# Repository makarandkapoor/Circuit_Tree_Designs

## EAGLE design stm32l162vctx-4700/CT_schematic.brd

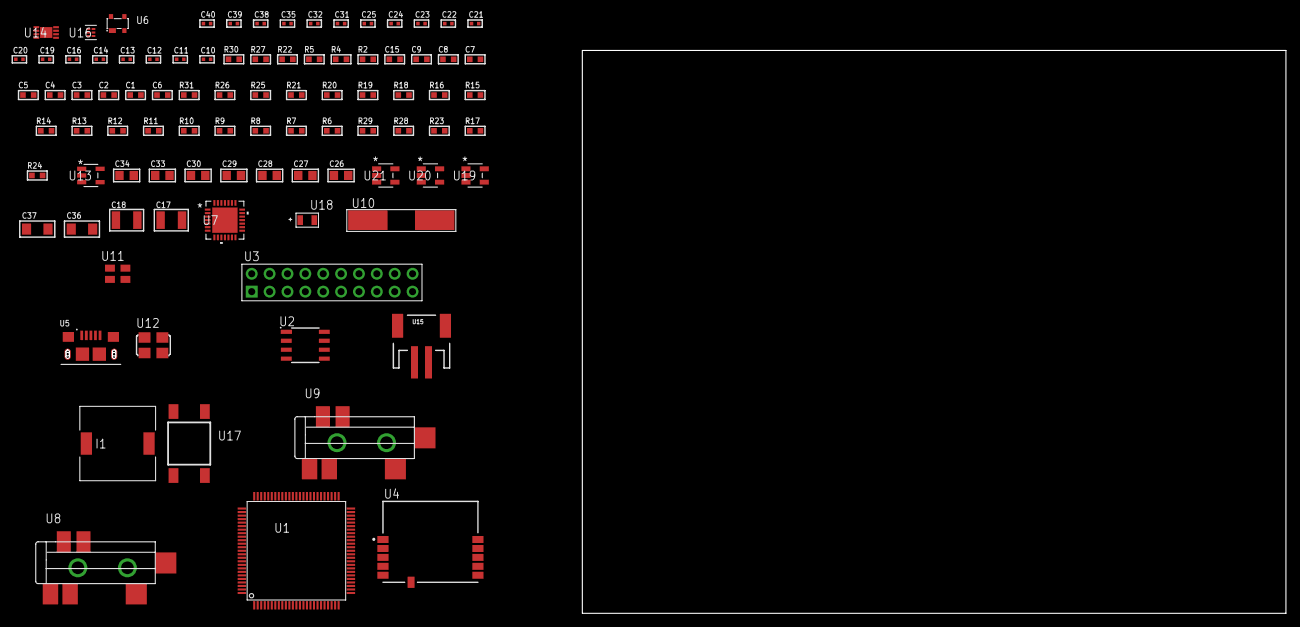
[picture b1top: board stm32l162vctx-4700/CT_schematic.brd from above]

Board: 2 copper layers, 91 parts (0 on the bottom side), 50 nets, no tracks yet.

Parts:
C1, C2, C3, C4, C5, C7: 1e-07; C0603
C6: 4.7e-06; C0603
C8: 1e-08; C0603
C9, C15: 1e-06; C0603
C10, C11: 1e-11; C0402
C12, C31, C32, C38, C39, C40: 1e-08; C0402
C13, C14, C16, C21, C22, C23, C24, C25, C35: 1e-07; C0402
C17, C18: 2.2e-05; C1210
C19, C20: 1e-09; C0402
C26, C27, C28, C29, C30, C33, C34: 1e-05; C0805
C36, C37: 1e-05; C1206
I1: 3.8e-06; DR1040
R2: 1000.0; R0603
R4, R5: 4700.0; R0603
R6, R7, R8, R9, R10, R11, R12, R13, R14, R15, R16, R25, R26, R31: 10000.0; R0603
R17: 100000.0; R0603
R18, R19, R20, R21: 47000.0; R0603
R22: 680.0; R0603
R23: 220000.0; R0603
R24: 1000000.0; R0603
R27: 9100.0; R0603
R28: 680000.0; R0603
R29: 120000.0; R0603
R30: 2000.0; R0603
U1: STM32L162VCTx; LQFP100
U2: AT25020B-SSHL-T; SOIC-8
U3: TST-110-05-T-D-RA
U4: SPBTLE-RF; XCVR_SPBTLE-RF
U5: 10118193-0001LF; FCI_10118193-0001LF
U6: prtr5v0u2ax; SOT143B
U7: WM8731CLSEFL; QFN-28
U8, U9: SJ-43515TS-SMT-TR
U10: ABLS-25.000MHZ-B2F-T
U11: ASEK-32.768KHz-ECST; ASEK
U12: ASFL1-12.288MHZ-EC-T; ASFL1
U13: ltc3406es5; TSOT-23-5
U14: MCP73831T-2ACI/MC; DFN8_2X3MC
U15: S2B-PH-SM4-TB(LF)(SN); JST-2-SMD
U16: TPS3895ADRYR; SON-6
U17: 4-1437565-2; SW_4-1437565-2
U18: Q65110A2395; LGM67K-G1J2-24-Z
U19, U20, U21: nc7sz125m5x; NC7SZ125M5X

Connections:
CLK_CRYSTAL_U1_12: C10.1, U1.12, U10.1
CLK_CRYSTAL_U1_13: C11.1, U1.13, U10.2
CLK_U1_8: U1.8, U11.3
CLK_U7_1: U7.1, U12.3
GND: C1.2, C2.2, C3.2, C4.2, C5.2, C6.2, C7.2, C8.2, C9.2, C10.2, C11.2, C12.2, C13.2, C14.2, C15.2, C16.2, C20.2, C21.2, C22.2, C23.2, C24.2, C25.2, C26.2, C27.2, C28.2, C29.2, C30.2, C31.2, C32.2, C33.2, C34.1, C34.2, C35.2, C36.2, C37.2, C38.2, C39.2, C40.2, R2.2, R6.2, R15.2, R17.2, R18.2, R19.2, R20.2, R21.2, R23.2, R27.2, R29.2, R30.2, U1.10, U1.19, U1.20, U1.27, U1.49, U1.74, U1.99, U2.4, U3.4, U3.6, U3.8, U3.10, U3.12, U3.14, U3.16, U3.18, U3.20, U4.6, U5.5, U5.6, U5.7, U5.8, U5.9, U6.1, U7.4, U7.15, U7.19, U7.25, U7.26, U7.29, U8.1, U9.1, U11.2, U12.2, U13.2, U14.6, U14.9, U15.2, U16.2, U18.C, U19.2, U19.3, U20.1, U20.3, U21.1, U21.3
INPUT_USBPOWER_5V: C36.1, R31.2, U5.1, U6.4, U14.1, U14.2
NET_U1_6: C7.1, U1.6
NET_U1_14: R5.1, U1.14, U21.4
NET_U1_22: C8.1, C9.1, U1.21, U1.22
NET_U1_94: R6.1, U1.94
NET_U1_98: U17.3, U17.4
NET_U2_3: R7.1, U2.3
NET_U2_7: R9.1, U2.7
NET_U3_19: R15.1, U3.19
NET_U4_11: R4.1, U4.11, U20.4
NET_U7_20: C25.1, C30.1, U7.20
NET_U8_2: C18.1, R20.1, U8.2
NET_U8_5: C17.1, R19.1, U8.5
NET_U9_5: C19.1, C20.1, R21.1, R22.1, U9.5
NET_U13_3: I1.1, U13.3
NET_U13_5: R23.1, R24.1, U13.5
NET_U13_ATNET_3: I1.2, R24.2
NET_U14_5: R31.1, U14.5
NET_U14_8: R30.1, U14.8
NET_U16_1: R26.1, R27.1, U16.1
NET_U16_3: R28.2, R29.1, U16.3
NET_U16_4: R25.1, U16.4, U19.4, U20.2, U21.2
NET_U17_1: R2.1, U17.1, U17.2
PROC_GPIO_TO_U4_SPI_IRQ: R18.1, U1.1, U4.4
PROC_I2S2_CK: U1.82, U7.7
PROC_I2S2_SD: U1.85, U7.8
PROC_I2S2_WS: U1.81, U7.9, U7.11
PROC_SPI1_MISO: U1.31, U4.8
PROC_SPI1_MOSI: U1.32, U4.9
PROC_SPI1_NSS: R16.1, U1.29, U4.10
PROC_SPI1_SCK: R17.1, U1.30, U4.7
PROC_SPI2_MISO: U1.53, U2.2
PROC_SPI2_MOSI: U1.54, U2.5
PROC_SPI2_NSS: R8.1, U1.51, U2.1
PROC_SPI2_SCK: U1.52, U2.6
PROC_SYS_JTCK_SWCLK: R13.1, U1.76, U3.9
PROC_SYS_JTDI: R11.1, U1.77, U3.5
PROC_SYS_JTDO_TRACESWO: U1.89, U3.13
PROC_SYS_JTMS_SWDIO: R12.1, U1.72, U3.7
PROC_SYS_JTRST: R10.1, U1.90, U3.3
PROC_USB_DM: U1.70, U5.2, U6.3
PROC_USB_DP: U1.71, U5.3, U6.2
RST_OUT_U3_SRESET_B: R14.1, U3.15, U19.1
VCC_S1_3V7: C33.1, C37.1, U13.4, U14.3, U14.4, U15.1
VCC_TIER1_3V3: C1.1, C2.1, C3.1, C4.1, C5.1, C6.1, C12.1, C13.1, C14.1, C15.1, C16.1, C21.1, C22.1, C23.1, C24.1, C26.1, C27.1, C28.1, C29.1, C31.1, C32.1, C34.2, C35.1, C38.1, C39.1, C40.1, I1.2, R4.2, R5.2, R7.2, R8.2, R9.2, R10.2, R11.2, R12.2, R13.2, R14.2, R16.2, R24.2, R25.2, R26.2, R28.1, U1.11, U1.28, U1.50, U1.75, U1.100, U2.8, U3.1, U3.2, U4.5, U7.3, U7.5, U7.12, U7.18, U11.4, U12.4, U16.6, U19.5, U20.5, U21.5

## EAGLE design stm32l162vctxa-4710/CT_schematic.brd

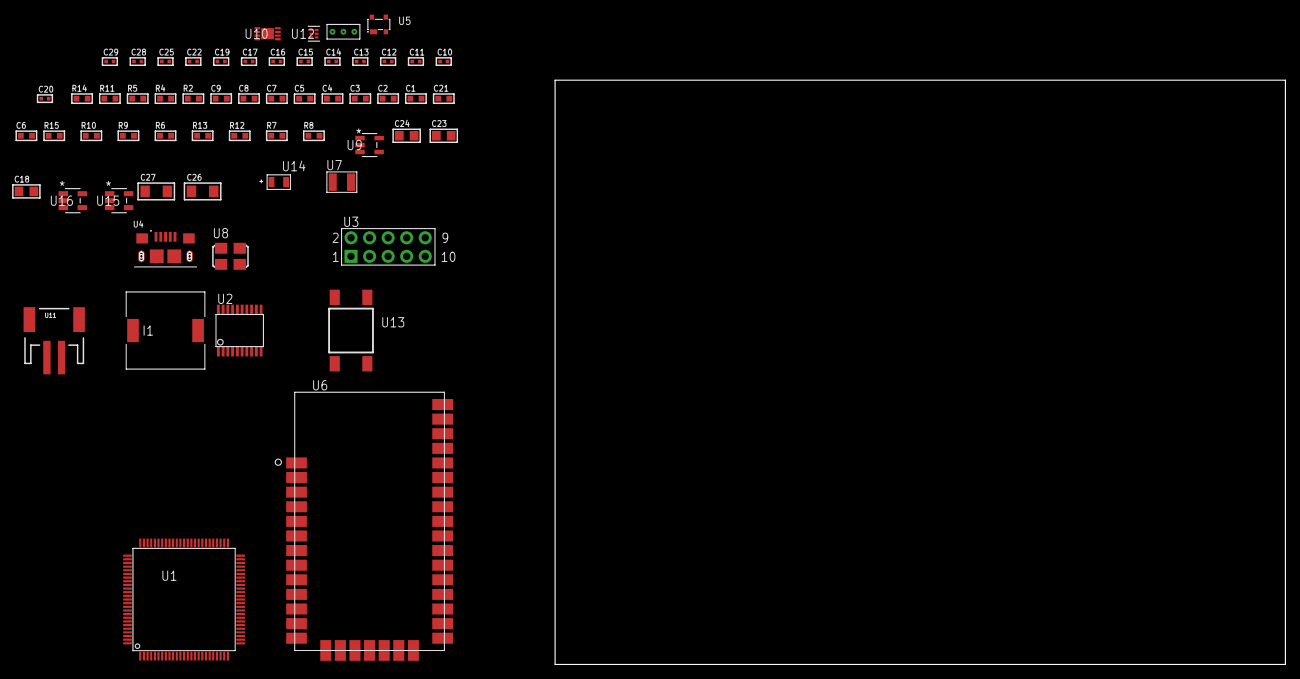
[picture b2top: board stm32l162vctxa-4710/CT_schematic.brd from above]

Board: 2 copper layers, 60 parts (0 on the bottom side), 43 nets, no tracks yet.

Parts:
C1, C2, C3, C4, C5, C7: 1e-07; C0603
C6: 4.7e-06; C0603
C8: 1e-08; C0603
C9: 1e-06; C0603
C10, C11: 1e-11; C0402
C12, C13, C14, C15, C16, C17, C19, C25: 1e-07; C0402
C18, C23, C24: 1e-05; C0805
C20: 4.7e-11; C0402
C21: 8.2e-12; C0603
C22, C28, C29: 1e-08; C0402
C26, C27: 1e-05; C1206
I1: 3.8e-06; DR1040
R2: 1000.0; R0603
R4, R5: 4700.0; R0603
R6, R9, R10, R15: 10000.0; R0603
R7: 220000.0; R0603
R8: 1000000.0; R0603
R11: 9100.0; R0603
R12: 680000.0; R0603
R13: 120000.0; R0603
R14: 2000.0; R0603
U1: STM32L162VCT6A; LQFP100
U2: SP3203ECY-L/TR; TSSOP20-I
U3: HTSS-105-01-G-D
U4: 10118193-0001LF; FCI_10118193-0001LF
U5: prtr5v0u2ax; SOT143B
U6: XB24CZ7UIS-004
U7: ABS07-32.768KHZ-7-T
U8: ASFL1-25MHZ-NCS; ASFL1
U9: ltc3406es5; TSOT-23-5
U10: MCP73831T-2ACI/MC; DFN8_2X3MC
U11: S2B-PH-SM4-TB(LF)(SN); JST-2-SMD
U12: TPS3895ADRYR; SON-6
U13: 4-1437565-2; SW_4-1437565-2
U14: Q65110A2395; LGM67K-G1J2-24-Z
U15, U16: nc7sz125m5x; NC7SZ125M5X
U17: Dummy; DUMMY_PACKAGE_131

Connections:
CLK_CRYSTAL_U1_8: C10.1, U1.8, U7.1
CLK_CRYSTAL_U1_9: C11.1, U1.9, U7.2
CLK_U1_12: U1.12, U8.3
GND: C1.2, C2.2, C3.2, C4.2, C5.2, C6.2, C7.2, C8.2, C9.2, C10.2, C11.2, C12.2, C13.2, C16.2, C17.2, C18.2, C19.2, C20.2, C21.2, C22.2, C23.2, C24.1, C24.2, C25.2, C26.2, C27.2, C28.2, C29.2, R2.2, R6.2, R7.2, R11.2, R13.2, R14.2, U1.10, U1.19, U1.20, U1.27, U1.49, U1.74, U1.99, U2.18, U3.9, U4.5, U4.6, U4.7, U4.8, U4.9, U5.1, U6.1, U6.11, U6.13, U6.22, U6.35, U8.2, U9.2, U10.6, U10.9, U11.2, U12.2, U14.C, U15.1, U15.3, U16.1, U16.3, U17.1
INPUT_USBPOWER_5V: C26.1, R15.2, U4.1, U5.4, U10.1, U10.2
NET_U1_6: C7.1, U1.6
NET_U1_14: R5.1, U1.14, U16.4
NET_U1_94: R6.1, U1.94
NET_U1_98: U13.3, U13.4
NET_U2_1: C14.1, U2.1
NET_U2_2: C16.1, U2.2
NET_U2_3: C14.2, U2.3
NET_U2_4: C15.1, U2.4
NET_U2_5: C15.2, U2.5
NET_U2_6: C17.1, U2.6
NET_U3_3: U2.14, U3.3
NET_U3_4: U2.13, U3.4
NET_U3_5: U2.17, U3.5
NET_U3_6: U2.16, U3.6
NET_U6_6: R4.1, U6.6, U15.4
NET_U9_3: I1.1, U9.3
NET_U9_5: R7.1, R8.1, U9.5
NET_U9_ATNET_3: I1.2, R8.2
NET_U10_5: R15.1, U10.5
NET_U10_8: R14.1, U10.8
NET_U12_1: R10.1, R11.1, U12.1
NET_U12_3: R12.2, R13.1, U12.3
NET_U12_4: R9.1, U12.4, U15.2, U16.2
NET_U13_1: R2.1, U13.1, U13.2
PROC_PE2: U1.1, U17.2
PROC_PE3: U1.2, U17.3
PROC_SPI1_MISO: U1.31, U6.17
PROC_SPI1_MOSI: U1.32, U6.16
PROC_SPI1_NSS: U1.29, U6.15
PROC_SPI1_SCK: U1.30, U6.14
PROC_USART2_CTS: U1.23, U2.8
PROC_USART2_RTS: U1.24, U2.10
PROC_USART2_RX: U1.26, U2.11
PROC_USART2_TX: U1.25, U2.7
PROC_USB_DM: U1.70, U4.2, U5.3
PROC_USB_DP: U1.71, U4.3, U5.2
VCC_S1_3V7: C23.1, C27.1, U9.4, U10.3, U10.4, U11.1
VCC_TIER1_3V3: C1.1, C2.1, C3.1, C4.1, C5.1, C6.1, C8.1, C9.1, C12.1, C13.1, C18.1, C19.1, C20.1, C21.1, C22.1, C24.2, C25.1, C28.1, C29.1, I1.2, R4.2, R5.2, R8.2, R9.2, R10.2, R12.1, U1.11, U1.21, U1.22, U1.28, U1.50, U1.75, U1.100, U2.12, U2.19, U6.2, U6.27, U8.4, U12.6, U15.5, U16.5

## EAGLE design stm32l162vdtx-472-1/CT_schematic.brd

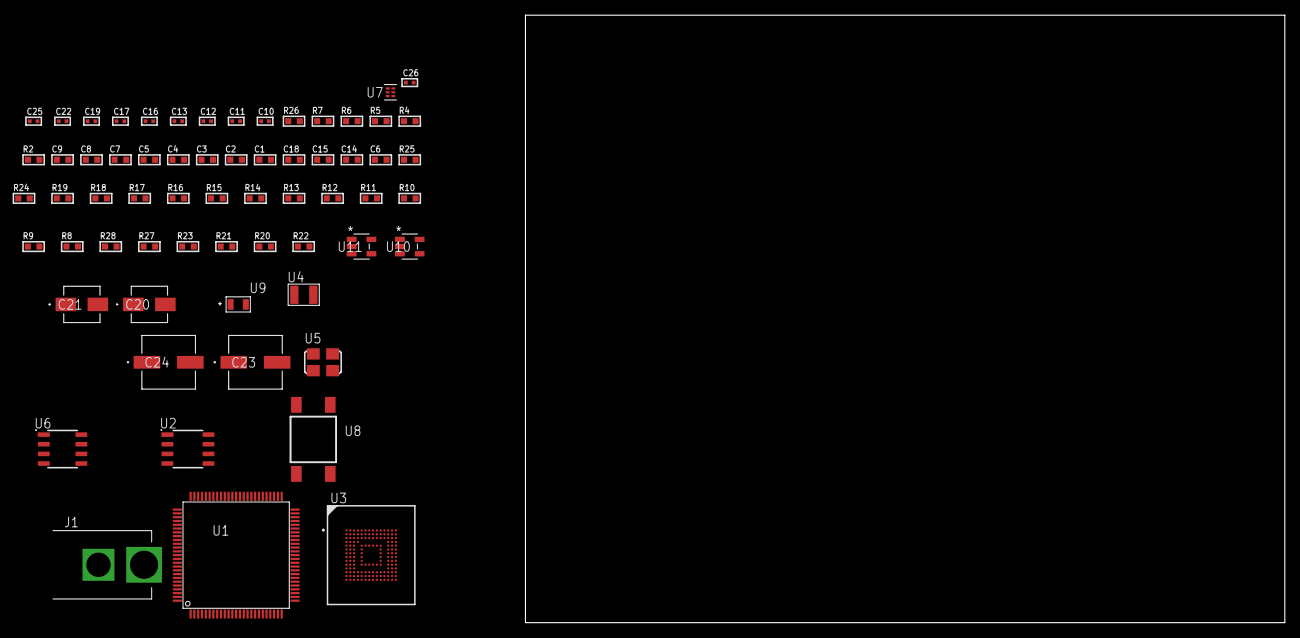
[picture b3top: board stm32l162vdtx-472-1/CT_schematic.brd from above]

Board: 2 copper layers, 100.0 x 80.0 mm, 64 parts (0 on the bottom side), 32 nets, no tracks yet.

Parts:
C1, C2, C3, C4, C5, C7: 1e-07; C0603
C6: 4.7e-06; C0603
C8: 1e-08; C0603
C9: 1e-06; C0603
C10, C11: 1e-11; C0402
C12, C19, C25, C26: 1e-08; C0402
C13, C16, C17, C22: 1e-07; C0402
C14, C15, C18: 2.2e-06; C0603
C20: 1e-06; EXV-9B
C21: 2.2e-06; EXV-9B
C23, C24: 0.0001; EXV-9H
J1: PJ-037B; PJ-037B_PACKAGE
R2: 1000.0; R0603
R4, R5: 4700.0; R0603
R6, R7: 2200.0; R0603
R8, R9, R24, R25: 10000.0; R0603
R10, R11, R12, R13, R14, R15, R16, R17, R18, R19: 34000.0; R0603
R20, R21, R23: 100000.0; R0603
R22: 164658.62; R0603
R26: 9100.0; R0603
R27: 680000.0; R0603
R28: 120000.0; R0603
U1: STM32L162VDT6; LQFP100
U2: M24M02-DRMN6TP; SOIC-8
U3: mtfc4gmcdm; TFBGA-153
U4: ABS07-32.768KHZ-7-T
U5: ASFL1-25MHZ-NCS; ASFL1
U6: LP2954AIMX/NOPB; LP2954
U7: TPS3895ADRYR; SON-6
U8: 4-1437565-2; SW_4-1437565-2
U9: Q65110A2395; LGM67K-G1J2-24-Z
U10, U11: nc7sz125m5x; NC7SZ125M5X

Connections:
CLK_CRYSTAL_U1_8: C10.1, U1.8, U4.1
CLK_CRYSTAL_U1_9: C11.1, U1.9, U4.2
CLK_U1_12: U1.12, U5.3
GND: C1.2, C2.2, C3.2, C4.2, C5.2, C6.2, C7.2, C8.2, C9.2, C10.2, C11.2, C12.2, C13.2, C14.2, C15.2, C16.2, C17.2, C18.2, C19.2, C20.2, C21.2, C22.2, C23.2, C24.2, C25.2, C26.2, J1.2, R2.2, R8.2, R9.2, R23.2, R26.2, R28.2, U1.10, U1.19, U1.20, U1.27, U1.49, U1.74, U1.99, U2.4, U3.C4, U3.E7, U3.G5, U3.H10, U3.K8, U3.N2, U3.N5, U3.P4, U3.P6, U5.2, U6.4, U7.2, U9.C, U10.1, U10.3, U11.1, U11.3
NET_U1_6: C7.1, U1.6
NET_U1_14: R5.1, U1.14, U11.4
NET_U1_92: R6.1, U1.92, U2.6
NET_U1_93: R7.1, U1.93, U2.5
NET_U1_94: R8.1, U1.94
NET_U1_98: U8.3, U8.4
NET_U2_3: R9.1, U2.3
NET_U3_C2: C15.1, C16.1, U3.C2
NET_U3_K5: R4.1, U3.K5, U10.4
NET_U6_3: R21.1, U6.3
NET_U6_5: R20.1, U6.5
NET_U6_7: R22.2, R23.1, U6.7
NET_U7_1: R25.1, R26.1, U7.1
NET_U7_3: R27.2, R28.1, U7.3
NET_U7_4: R24.1, U7.4, U10.2, U11.2
NET_U8_1: R2.1, U8.1, U8.2
PROC_SDIO_CK: R19.1, U1.80, U3.M6
PROC_SDIO_CMD: R18.1, U1.83, U3.M5
PROC_SDIO_D0: R10.1, U1.65, U3.A3
PROC_SDIO_D1: R11.1, U1.66, U3.A4
PROC_SDIO_D2: R12.1, U1.78, U3.A5
PROC_SDIO_D3: R13.1, U1.79, U3.B2
PROC_SDIO_D4: R14.1, U1.95, U3.B3
PROC_SDIO_D5: R15.1, U1.96, U3.B4
PROC_SDIO_D6: R16.1, U1.63, U3.B5
PROC_SDIO_D7: R17.1, U1.64, U3.B6
VCC_S1_7V2: C20.1, C23.1, C24.1, J1.1, R21.2, U6.8
VCC_TIER1_3V3: C1.1, C2.1, C3.1, C4.1, C5.1, C6.1, C8.1, C9.1, C12.1, C13.1, C14.1, C17.1, C18.1, C19.1, C21.1, C22.1, C25.1, C26.1, R4.2, R5.2, R6.2, R7.2, R10.2, R11.2, R12.2, R13.2, R14.2, R15.2, R16.2, R17.2, R18.2, R19.2, R20.2, R22.1, R24.2, R25.2, R27.1, U1.11, U1.21, U1.22, U1.28, U1.50, U1.75, U1.100, U2.8, U3.C6, U3.E6, U3.F5, U3.J10, U3.K9, U3.M4, U3.N4, U3.P3, U3.P5, U5.4, U6.1, U7.6, U10.5, U11.5

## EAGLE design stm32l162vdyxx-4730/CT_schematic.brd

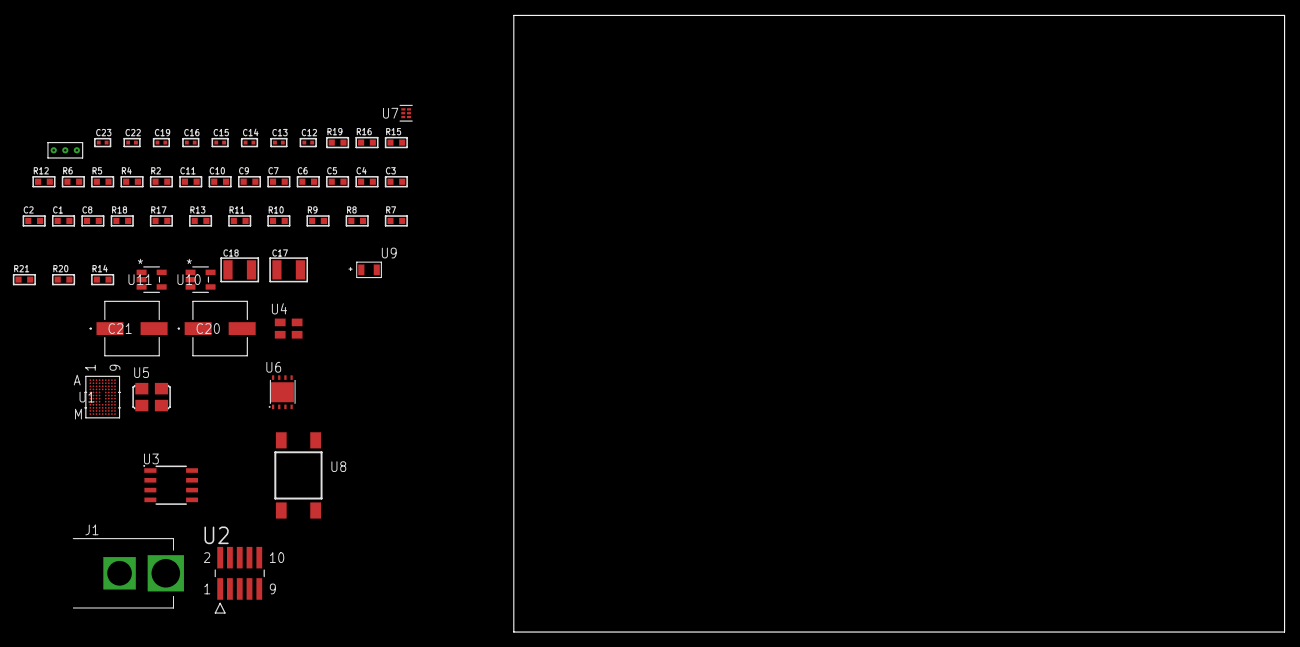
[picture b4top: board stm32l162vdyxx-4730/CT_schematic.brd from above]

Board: 2 copper layers, 100.0 x 80.0 mm, 55 parts (0 on the bottom side), 27 nets, no tracks yet.

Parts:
C1, C2, C3, C4, C5, C6, C7, C9: 1e-07; C0603
C8: 4.7e-06; C0603
C10: 1e-08; C0603
C11: 1e-06; C0603
C12, C19: 1e-07; C0402
C13, C14, C15, C16, C22, C23: 1e-08; C0402
C17, C18: 1e-05; C1210
C20, C21: 0.0001; EXV-9H
J1: PJ-037B; PJ-037B_PACKAGE
R2, R16: 1000.0; R0603
R4: 4700.0; R0603
R5, R6: 2200.0; R0603
R7, R8, R9, R10, R11, R13, R17, R18: 10000.0; R0603
R12: 5.0; R0603
R14: 100000.0; R0603
R15: 2231.0; R0603
R19: 9100.0; R0603
R20: 680000.0; R0603
R21: 120000.0; R0603
U1: STM32L162VDY6X; WLCSP104
U2: FTSH-105-01-L-DV-K; SAMTEC_FTSH-105-01-L-DV-K
U3: M24M02-DRMN6TP; SOIC-8
U4: ASEK-32.768KHz-ECST; ASEK
U5: ASFL1-25MHZ-NCS; ASFL1
U6: LP3878SDX-ADJ/NOPB; WSON-8
U7: TPS3895ADRYR; SON-6
U8: 4-1437565-2; SW_4-1437565-2
U9: Q65110A2395; LGM67K-G1J2-24-Z
U10, U11: nc7sz125m5x; NC7SZ125M5X
U12: Dummy; DUMMY_PACKAGE_121

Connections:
CLK_U1_D8: U1.D8, U4.3
CLK_U1_F8: U1.F8, U5.3
GND: C1.2, C2.2, C3.2, C4.2, C5.2, C6.2, C7.2, C8.2, C9.2, C10.2, C11.2, C12.2, C13.2, C14.2, C15.2, C16.2, C17.2, C18.2, C19.2, C20.2, C21.2, C22.2, C23.2, J1.2, R2.2, R7.2, R11.2, R12.2, R13.2, R16.2, R19.2, R21.2, U1.A1, U1.C7, U1.D2, U1.E8, U1.H8, U1.J9, U1.K8, U1.L2, U1.M1, U2.3, U2.5, U3.4, U4.2, U5.2, U6.3, U6.PAD, U7.2, U9.C, U10.2, U10.3, U11.1, U11.3, U12.1
NET_U1_A7: R7.1, U1.A7
NET_U1_B6: R6.1, U1.B6, U3.5
NET_U1_C5: R5.1, U1.C5, U3.6
NET_U1_E7: C9.1, U1.E7
NET_U1_F7: R4.1, U1.F7, U11.4
NET_U1_M8: U8.3, U8.4
NET_U2_9: R12.1, U2.9
NET_U3_3: R13.1, U3.3
NET_U6_1: C16.1, U6.1
NET_U6_6: R15.2, R16.1, U6.6
NET_U6_8: R14.1, U6.8
NET_U7_1: R18.1, R19.1, U7.1
NET_U7_3: R20.2, R21.1, U7.3
NET_U7_4: R17.1, U7.4, U10.4, U11.2
NET_U8_1: R2.1, U8.1, U8.2
PROC_SYS_JTCK_SWCLK: R11.1, U1.D3, U2.4
PROC_SYS_JTDI: R9.1, U1.B1, U2.8
PROC_SYS_JTDO_TRACESWO: U1.B5, U2.6
PROC_SYS_JTMS_SWDIO: R10.1, U1.E3, U2.2
PROC_TIM10_CH1: U1.B7, U12.2
PROC_TIM11_CH1: U1.A8, U12.3
RST_OUT_U2_JTAG_RST_B: R8.1, U2.10, U10.1
VCC_S1_12V4: C17.1, C20.1, C21.1, J1.1, R14.2, U6.4
VCC_TIER1_3V3: C1.1, C2.1, C3.1, C4.1, C5.1, C6.1, C7.1, C8.1, C10.1, C11.1, C12.1, C13.1, C14.1, C15.1, C18.1, C19.1, C22.1, C23.1, R4.2, R5.2, R6.2, R8.2, R9.2, R10.2, R15.1, R17.2, R18.2, R20.1, U1.A9, U1.B8, U1.C1, U1.E9, U1.G6, U1.G7, U1.K3, U1.L8, U1.M9, U2.1, U3.8, U4.4, U5.4, U6.5, U7.6, U10.5, U11.5

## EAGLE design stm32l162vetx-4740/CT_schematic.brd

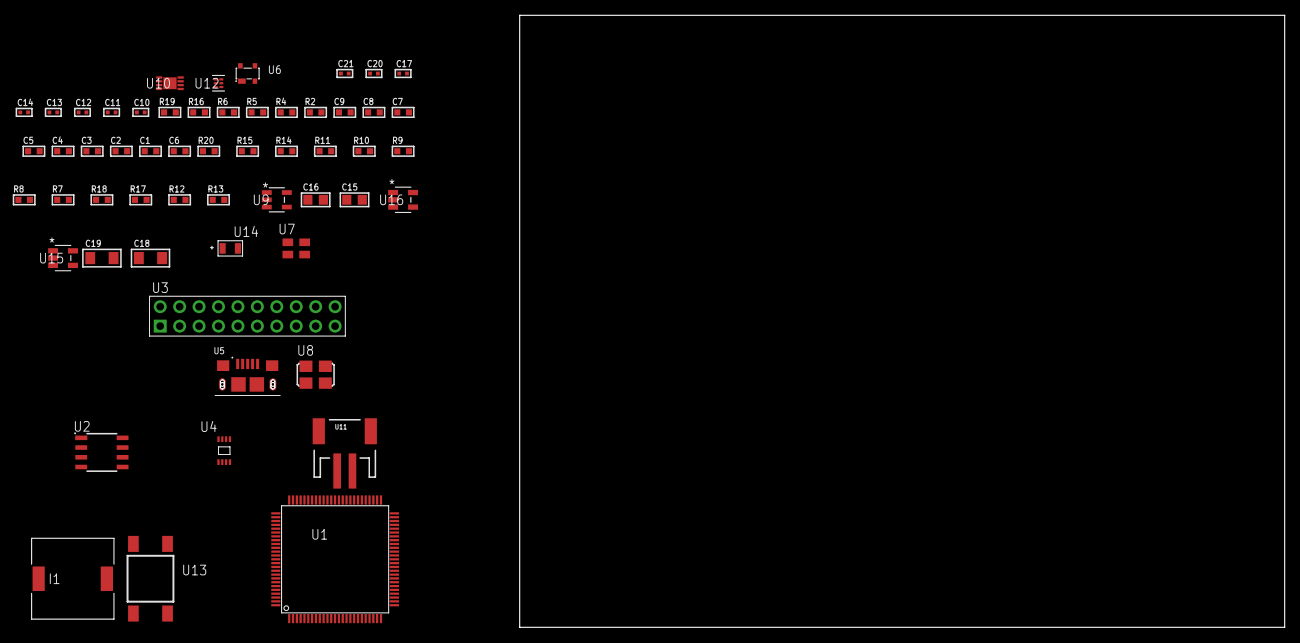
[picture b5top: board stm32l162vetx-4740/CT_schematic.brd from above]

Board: 2 copper layers, 56 parts (0 on the bottom side), 33 nets, no tracks yet.

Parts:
C1, C2, C3, C4, C5, C7: 1e-07; C0603
C6: 4.7e-06; C0603
C8: 1e-08; C0603
C9: 1e-06; C0603
C10, C12, C13, C14, C20, C21: 1e-08; C0402
C11, C17: 1e-07; C0402
C15, C16: 1e-05; C0805
C18, C19: 1e-05; C1206
I1: 3.8e-06; DR1040
R2: 1000.0; R0603
R4: 4700.0; R0603
R5, R6: 2200.0; R0603
R7, R8, R9, R10, R11, R14, R15, R20: 10000.0; R0603
R12: 220000.0; R0603
R13: 1000000.0; R0603
R16: 9100.0; R0603
R17: 680000.0; R0603
R18: 120000.0; R0603
R19: 2000.0; R0603
U1: STM32L162VET6; LQFP100
U2: AT25160B-SSHL-T; SOIC-8
U3: TST-110-05-T-D-RA
U4: 24AA08T-I/MNY; TDFN-8/6MM
U5: 10118193-0001LF; FCI_10118193-0001LF
U6: prtr5v0u2ax; SOT143B
U7: ASEK-32.768KHz-ECST; ASEK
U8: ASFL1-25MHZ-NCS; ASFL1
U9: ltc3406es5; TSOT-23-5
U10: MCP73831T-2ACI/MC; DFN8_2X3MC
U11: S2B-PH-SM4-TB(LF)(SN); JST-2-SMD
U12: TPS3895ADRYR; SON-6
U13: 4-1437565-2; SW_4-1437565-2
U14: Q65110A2395; LGM67K-G1J2-24-Z
U15, U16: nc7sz125m5x; NC7SZ125M5X

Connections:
CLK_U1_8: U1.8, U7.3
CLK_U1_12: U1.12, U8.3
GND: C1.2, C2.2, C3.2, C4.2, C5.2, C6.2, C7.2, C8.2, C9.2, C10.2, C11.2, C12.2, C13.2, C14.2, C15.2, C16.1, C16.2, C17.2, C18.2, C19.2, C20.2, C21.2, R2.2, R7.2, R12.2, R16.2, R18.2, R19.2, U1.10, U1.19, U1.20, U1.27, U1.49, U1.74, U1.99, U2.4, U3.4, U3.6, U3.8, U3.10, U3.12, U3.14, U3.16, U3.18, U3.20, U4.4, U5.5, U5.6, U5.7, U5.8, U5.9, U6.1, U7.2, U8.2, U9.2, U10.6, U10.9, U11.2, U12.2, U14.C, U15.2, U15.3, U16.1, U16.3
INPUT_USBPOWER_5V: C18.1, R20.2, U5.1, U6.4, U10.1, U10.2
NET_U1_6: C7.1, U1.6
NET_U1_14: R4.1, U1.14, U16.4
NET_U1_92: R5.1, U1.92, U4.6
NET_U1_93: R6.1, U1.93, U4.5
NET_U1_94: R7.1, U1.94
NET_U1_98: U13.3, U13.4
NET_U2_3: R8.1, U2.3
NET_U2_7: R10.1, U2.7
NET_U9_3: I1.1, U9.3
NET_U9_5: R12.1, R13.1, U9.5
NET_U9_ATNET_3: I1.2, R13.2
NET_U10_5: R20.1, U10.5
NET_U10_8: R19.1, U10.8
NET_U12_1: R15.1, R16.1, U12.1
NET_U12_3: R17.2, R18.1, U12.3
NET_U12_4: R14.1, U12.4, U15.4, U16.2
NET_U13_1: R2.1, U13.1, U13.2
PROC_SPI1_MISO: U1.31, U2.2
PROC_SPI1_MOSI: U1.32, U2.5
PROC_SPI1_NSS: R9.1, U1.29, U2.1
PROC_SPI1_SCK: U1.30, U2.6
PROC_SYS_JTCK_SWCLK: U1.76, U3.9
PROC_SYS_JTDO_TRACESWO: U1.89, U3.13
PROC_SYS_JTMS_SWDIO: U1.72, U3.7
PROC_USB_DM: U1.70, U5.2, U6.3
PROC_USB_DP: U1.71, U5.3, U6.2
RST_OUT_U3_SRESET_B: R11.1, U3.15, U15.1
VCC_S1_3V7: C15.1, C19.1, U9.4, U10.3, U10.4, U11.1
VCC_TIER1_3V3: C1.1, C2.1, C3.1, C4.1, C5.1, C6.1, C8.1, C9.1, C10.1, C11.1, C12.1, C13.1, C14.1, C16.2, C17.1, C20.1, C21.1, I1.2, R4.2, R5.2, R6.2, R8.2, R9.2, R10.2, R11.2, R13.2, R14.2, R15.2, R17.1, U1.11, U1.21, U1.22, U1.28, U1.50, U1.75, U1.100, U2.8, U3.1, U4.7, U4.8, U7.4, U8.4, U12.6, U15.5, U16.5

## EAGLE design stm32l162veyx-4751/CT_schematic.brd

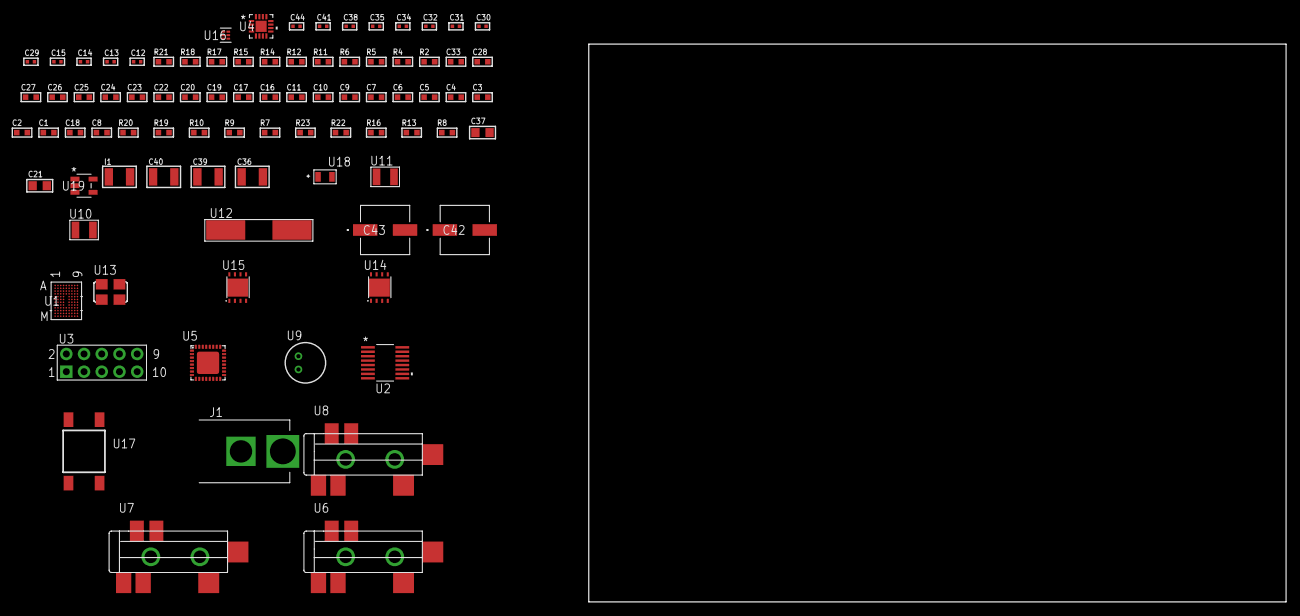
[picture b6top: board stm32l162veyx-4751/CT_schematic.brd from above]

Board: 2 copper layers, 100.0 x 80.0 mm, 86 parts (0 on the bottom side), 56 nets, no tracks yet.

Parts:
C1, C2, C3, C4, C5, C6, C7, C9: 1e-07; C0603
C8: 4.7e-06; C0603
C10: 1e-08; C0603
C11, C16, C17, C19, C20, C22, C23, C24, C25, C26, C27, C28, C33: 1e-06; C0603
C12, C13, C14, C15: 1e-11; C0402
C18: 2.2e-07; C0603
C21: 4.7e-06; C0805
C29, C30, C31, C32, C41: 1e-07; C0402
C34, C35, C38, C44: 1e-08; C0402
C36, C39, C40: 1e-05; C1210
C37: 1e-05; C0805
C42, C43: 0.0001; EXV-9H
I1: 1e-05; L1210
J1: PJ-037B; PJ-037B_PACKAGE
R2, R15, R18: 1000.0; R0603
R4: 4700.0; R0603
R5, R6: 2200.0; R0603
R7, R9, R10, R19, R20: 10000.0; R0603
R8, R13, R16: 100000.0; R0603
R11, R12: 1270.0; R0603
R14: 200.0; R0603
R17: 2231.0; R0603
R21: 9100.0; R0603
R22: 680000.0; R0603
R23: 120000.0; R0603
U1: STM32L162VEY6TR; WLCSP104
U2: LTC2804CGN-1#PBF; SSOP-16
U3: HTSS-105-01-G-D
U4: M41T65Q6F; M41T65_QFN-16
U5: SGTL5000XNAA3; QFN-32
U6, U7, U8: SJ-43515TS-SMT-TR
U9: WM-64PCT; WM-64PC
U10, U11: ABS07-32.768KHZ-7-T
U12: ABLS-25.000MHZ-B2F-T
U13: ASFL-24.57MHZ-NCS; ASFL1
U14, U15: LP3878SDX-ADJ/NOPB; WSON-8
U16: TPS3895ADRYR; SON-6
U17: 4-1437565-2; SW_4-1437565-2
U18: Q65110A2395; LGM67K-G1J2-24-Z
U19: nc7sz125m5x; NC7SZ125M5X

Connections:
CLK_CRYSTAL_U1_D8: C12.1, U1.D8, U11.1
CLK_CRYSTAL_U1_D9: C13.1, U1.D9, U11.2
CLK_CRYSTAL_U1_F8: C14.1, U1.F8, U12.1
CLK_CRYSTAL_U1_F9: C15.1, U1.F9, U12.2
CLK_CRYSTAL_U4_1: U4.1, U10.1
CLK_CRYSTAL_U4_2: U4.2, U10.2
CLK_U5_21: U5.21, U13.3
GND: C1.2, C2.2, C3.2, C4.2, C5.2, C6.2, C7.2, C8.2, C9.2, C10.2, C11.2, C12.2, C13.2, C14.2, C15.2, C16.2, C17.2, C19.2, C20.2, C21.2, C29.2, C30.2, C31.2, C32.2, C33.2, C34.2, C35.2, C36.2, C37.2, C38.2, C39.2, C40.2, C41.2, C42.2, C43.2, C44.2, J1.2, R2.2, R7.2, R12.2, R15.2, R18.2, R21.2, R23.2, U1.A1, U1.C7, U1.D2, U1.E8, U1.H8, U1.J9, U1.K8, U1.L2, U1.M1, U2.8, U3.9, U4.3, U4.5, U4.17, U5.1, U5.3, U5.7, U5.EXP, U7.1, U8.1, U9.2, U13.2, U14.3, U14.PAD, U15.3, U15.PAD, U16.2, U18.C, U19.1, U19.3
NET_U1_A7: R7.1, U1.A7
NET_U1_B6: R6.1, U1.B6, U4.9
NET_U1_C5: R5.1, U1.C5, U4.10
NET_U1_E7: C9.1, U1.E7
NET_U1_F7: R4.1, U1.F7, U19.4
NET_U1_M8: U17.3, U17.4
NET_U2_6: C16.1, U2.6
NET_U2_7: C18.1, I1.2, U2.7
NET_U2_9: C17.1, U2.9
NET_U2_10: C18.2, U2.10
NET_U2_11: R8.1, U2.11
NET_U3_3: U2.1, U3.3
NET_U3_4: U2.2, U3.4
NET_U3_5: U2.3, U3.5
NET_U3_6: U2.4, U3.6
NET_U4_4: R9.1, U4.4
NET_U4_11: R10.1, U4.11
NET_U5_10: C32.1, U5.10
NET_U5_29: R11.1, U5.29
NET_U5_31: R12.1, U5.31
NET_U6_1: U5.4, U6.1
NET_U6_2: U5.2, U6.2
NET_U6_5: U5.6, U6.5
NET_U7_2: C23.1, U7.2
NET_U7_5: C22.1, U7.5
NET_U8_2: C25.1, C26.1, U8.2
NET_U8_5: C24.1, U8.5
NET_U8_13: C25.2, C26.2
NET_U9_1: C27.1, C28.1, C33.1, U5.16, U9.1
NET_U9_15: C27.2, C28.2
NET_U14_1: C35.1, U14.1
NET_U14_6: R14.2, R15.1, U14.6
NET_U14_8: R13.1, U14.8
NET_U15_1: C38.1, U15.1
NET_U15_6: R17.2, R18.1, U15.6
NET_U15_8: R16.1, U15.8
NET_U16_1: R20.1, R21.1, U16.1
NET_U16_3: R22.2, R23.1, U16.3
NET_U16_4: R19.1, U16.4, U19.2
NET_U17_1: R2.1, U17.1, U17.2
PROC_I2S2_CK: U1.D4, U5.24
PROC_I2S2_SD: U1.A3, U5.26
PROC_I2S2_WS: U1.A2, U5.23
PROC_UART4_RX: U1.C2, U2.16
PROC_UART4_TX: U1.E4, U2.14
VCC_S1_11V6: C36.1, C39.1, C42.1, C43.1, J1.1, R13.2, R16.2, U14.4, U15.4
VCC_TIER1_1V2: C29.1, C37.1, R14.1, U5.30, U14.5
VCC_TIER1_3V3: C1.1, C2.1, C3.1, C4.1, C5.1, C6.1, C7.1, C8.1, C10.1, C11.1, C19.1, C20.1, C21.1, C30.1, C31.1, C34.1, C40.1, C41.1, C44.1, I1.1, R4.2, R5.2, R6.2, R8.2, R9.2, R10.2, R11.2, R17.1, R19.2, R20.2, R22.1, U1.A9, U1.B8, U1.C1, U1.E9, U1.G6, U1.G7, U1.K3, U1.L8, U1.M9, U2.5, U2.12, U4.14, U5.5, U5.20, U13.4, U15.5, U16.6, U19.5

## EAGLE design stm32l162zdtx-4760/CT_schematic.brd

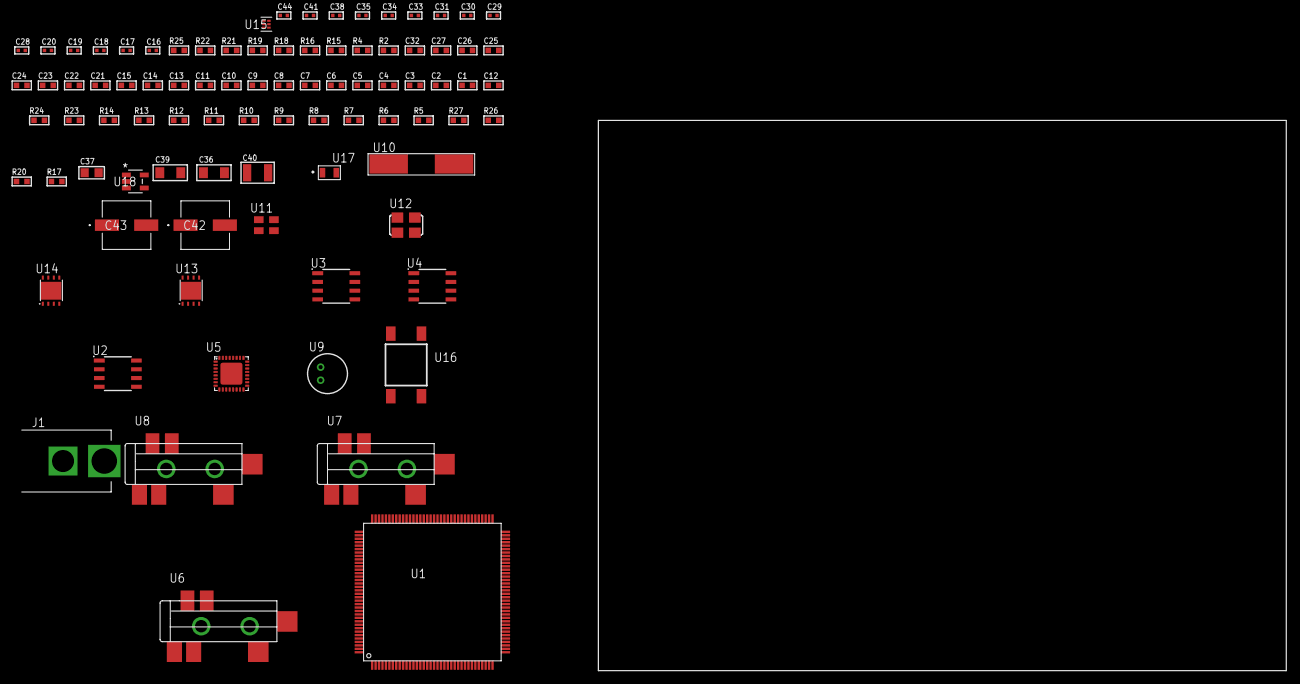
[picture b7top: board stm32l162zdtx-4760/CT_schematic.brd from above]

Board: 2 copper layers, 100.0 x 80.0 mm, 88 parts (0 on the bottom side), 53 nets, no tracks yet.

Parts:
C1, C2, C3, C4, C5, C6, C7, C8, C9, C10, C11, C13: 1e-07; C0603
C12: 4.7e-06; C0603
C14: 1e-08; C0603
C15, C21, C22, C23, C24, C25, C26, C27, C32: 1e-06; C0603
C16, C17: 1e-11; C0402
C18, C19, C20, C33, C34, C35, C38, C44: 1e-08; C0402
C28, C29, C30, C31, C41: 1e-07; C0402
C36, C39: 1e-05; C1206
C37: 1e-05; C0805
C40: 1e-05; C1210
C42, C43: 0.0001; EXV-9H
J1: PJ-037B; PJ-037B_PACKAGE
R2, R19, R22: 1000.0; R0603
R4: 4700.0; R0603
R5, R6, R7, R8, R9, R10, R11, R12, R13, R14, R23, R24: 10000.0; R0603
R15, R16: 1270.0; R0603
R17, R20: 100000.0; R0603
R18: 200.0; R0603
R21: 2231.0; R0603
R25: 9100.0; R0603
R26: 680000.0; R0603
R27: 120000.0; R0603
U1: STM32L162ZDT6; LQFP144
U2: AT25160B-SSHL-T; SOIC-8
U3: AT25512N-SH-T; SOIC-8
U4: AT25M02-SSHD-T; SOIC-8
U5: SGTL5000XNAA3; QFN-32
U6, U7, U8: SJ-43515TS-SMT-TR
U9: WM-64PCT; WM-64PC
U10: ABLS-25.000MHZ-B2F-T
U11: ASEK-32.768KHz-ECST; ASEK
U12: ASFL-24.57MHZ-NCS; ASFL1
U13, U14: LP3878SDX-ADJ/NOPB; WSON-8
U15: TPS3895ADRYR; SON-6
U16: 4-1437565-2; SW_4-1437565-2
U17: Q65110A2395; LGM67K-G1J2-24-Z
U18: nc7sz125m5x; NC7SZ125M5X

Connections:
CLK_CRYSTAL_U1_23: C16.1, U1.23, U10.1
CLK_CRYSTAL_U1_24: C17.1, U1.24, U10.2
CLK_U1_8: U1.8, U11.3
CLK_U5_21: U5.21, U12.3
GND: C1.2, C2.2, C3.2, C4.2, C5.2, C6.2, C7.2, C8.2, C9.2, C10.2, C11.2, C12.2, C13.2, C14.2, C15.2, C16.2, C17.2, C18.2, C19.2, C20.2, C28.2, C29.2, C30.2, C31.2, C32.2, C33.2, C34.2, C35.2, C36.2, C37.2, C38.2, C39.2, C40.2, C41.2, C42.2, C43.2, C44.2, J1.2, R2.2, R5.2, R16.2, R19.2, R22.2, R25.2, R27.2, U1.16, U1.30, U1.31, U1.38, U1.51, U1.61, U1.71, U1.83, U1.94, U1.107, U1.120, U1.130, U1.143, U2.4, U3.4, U4.4, U5.1, U5.3, U5.7, U5.EXP, U7.1, U8.1, U9.2, U11.2, U12.2, U13.3, U13.PAD, U14.3, U14.PAD, U15.2, U17.C, U18.1, U18.3
NET_U1_6: C13.1, U1.6
NET_U1_25: R4.1, U1.25, U18.4
NET_U1_138: R5.1, U1.138
NET_U1_142: U16.3, U16.4
NET_U2_3: R6.1, U2.3
NET_U2_7: R8.1, U2.7
NET_U3_3: R9.1, U3.3
NET_U3_7: R11.1, U3.7
NET_U4_3: R12.1, U4.3
NET_U4_7: R14.1, U4.7
NET_U5_10: C31.1, U5.10
NET_U5_29: R15.1, U5.29
NET_U5_31: R16.1, U5.31
NET_U6_1: U5.4, U6.1
NET_U6_2: U5.2, U6.2
NET_U6_5: U5.6, U6.5
NET_U7_2: C22.1, U7.2
NET_U7_5: C21.1, U7.5
NET_U8_2: C24.1, C25.1, U8.2
NET_U8_5: C23.1, U8.5
NET_U8_13: C24.2, C25.2
NET_U9_1: C26.1, C27.1, C32.1, U5.16, U9.1
NET_U9_15: C26.2, C27.2
NET_U13_1: C35.1, U13.1
NET_U13_6: R18.2, R19.1, U13.6
NET_U13_8: R17.1, U13.8
NET_U14_1: C38.1, U14.1
NET_U14_6: R21.2, R22.1, U14.6
NET_U14_8: R20.1, U14.8
NET_U15_1: R24.1, R25.1, U15.1
NET_U15_3: R26.2, R27.1, U15.3
NET_U15_4: R23.1, U15.4, U18.2
NET_U16_1: R2.1, U16.1, U16.2
PROC_I2S2_CK: U1.74, U5.24
PROC_I2S2_SD: U1.76, U5.26
PROC_I2S2_WS: U1.73, U5.23
PROC_SPI1_MISO: U1.42, U3.2
PROC_SPI1_MOSI: U1.43, U3.5
PROC_SPI1_NSS: R10.1, U1.65, U3.1
PROC_SPI1_SCK: U1.41, U3.6
PROC_SPI2_MISO: U1.75, U2.2
PROC_SPI2_MOSI: U1.118, U2.5
PROC_SPI2_NSS: R7.1, U1.114, U2.1
PROC_SPI2_SCK: U1.115, U2.6
PROC_SPI3_NSS: R13.1, U4.1
VCC_S1_8V3: C36.1, C39.1, C42.1, C43.1, J1.1, R17.2, R20.2, U13.4, U14.4
VCC_TIER1_1V2: C28.1, C37.1, R18.1, U5.30, U13.5
VCC_TIER1_3V3: C1.1, C2.1, C3.1, C4.1, C5.1, C6.1, C7.1, C8.1, C9.1, C10.1, C11.1, C12.1, C14.1, C15.1, C18.1, C19.1, C20.1, C29.1, C30.1, C33.1, C34.1, C40.1, C41.1, C44.1, R4.2, R6.2, R7.2, R8.2, R9.2, R10.2, R11.2, R12.2, R13.2, R14.2, R15.2, R21.1, R23.2, R24.2, R26.1, U1.17, U1.32, U1.33, U1.39, U1.52, U1.62, U1.72, U1.84, U1.95, U1.108, U1.121, U1.131, U1.144, U2.8, U3.8, U4.8, U5.5, U5.20, U11.4, U12.4, U14.5, U15.6, U18.5

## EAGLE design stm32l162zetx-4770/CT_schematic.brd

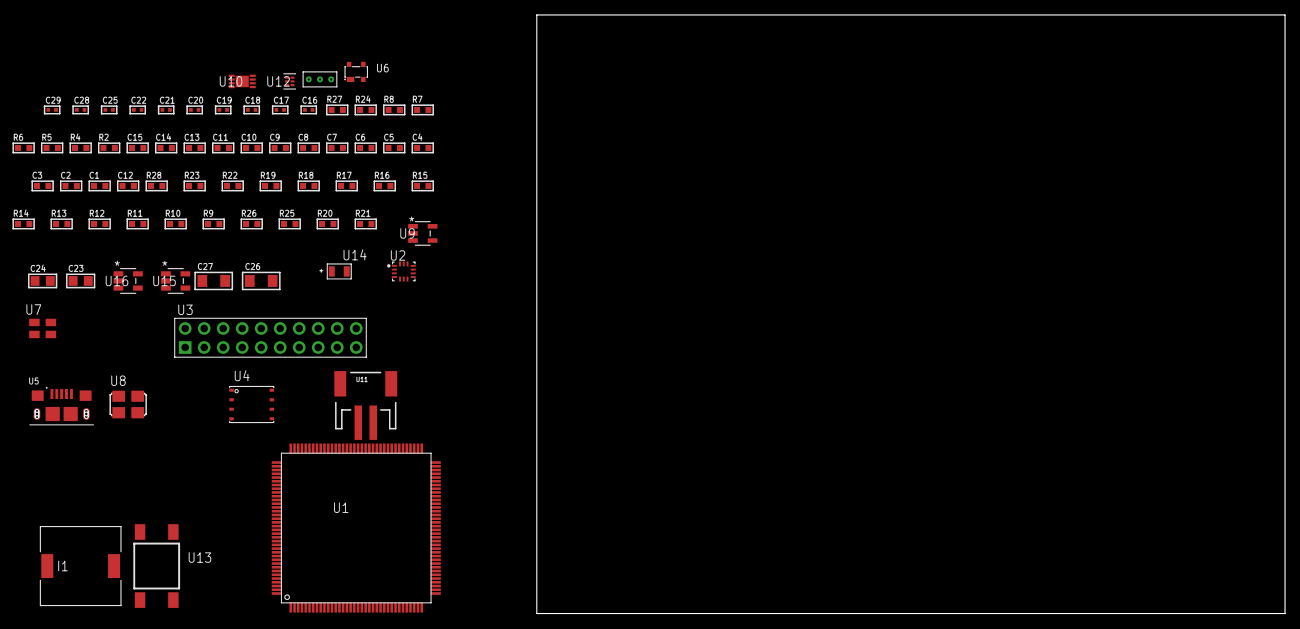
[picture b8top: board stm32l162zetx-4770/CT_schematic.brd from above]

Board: 2 copper layers, 167.1 x 80.0 mm, 73 parts (0 on the bottom side), 40 nets, no tracks yet.

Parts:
C1, C2, C3, C4, C5, C6, C7, C8, C9, C10, C11, C13: 1e-07; C0603
C12: 4.7e-06; C0603
C14: 1e-08; C0603
C15: 1e-06; C0603
C16, C17, C18, C19, C25: 1e-07; C0402
C20, C21, C22, C28, C29: 1e-08; C0402
C23, C24: 1e-05; C0805
C26, C27: 1e-05; C1206
I1: 3.8e-06; DR1040
R2: 1000.0; R0603
R4: 4700.0; R0603
R5, R6, R7, R8: 2200.0; R0603
R9, R10, R11, R12, R13, R14, R15, R16, R17, R18, R19, R22, R23, R28: 10000.0; R0603
R20: 220000.0; R0603
R21: 1000000.0; R0603
R24: 9100.0; R0603
R25: 680000.0; R0603
R26: 120000.0; R0603
R27: 2000.0; R0603
U1: STM32L162ZET6; LQFP144
U2: BMG250; LGA-14
U3: TST-110-05-T-D-RA
U4: 24AA512-I/MF; DFN8-S
U5: 10118193-0001LF; FCI_10118193-0001LF
U6: prtr5v0u2ax; SOT143B
U7: ASEK-32.768KHz-ECST; ASEK
U8: ASFL1-25MHZ-NCS; ASFL1
U9: ltc3406es5; TSOT-23-5
U10: MCP73831T-2ACI/MC; DFN8_2X3MC
U11: S2B-PH-SM4-TB(LF)(SN); JST-2-SMD
U12: TPS3895ADRYR; SON-6
U13: 4-1437565-2; SW_4-1437565-2
U14: Q65110A2395; LGM67K-G1J2-24-Z
U15, U16: nc7sz125m5x; NC7SZ125M5X
U17: Dummy; DUMMY_PACKAGE_165

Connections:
CLK_U1_8: U1.8, U7.3
CLK_U1_23: U1.23, U8.3
GND: C1.2, C2.2, C3.2, C4.2, C5.2, C6.2, C7.2, C8.2, C9.2, C10.2, C11.2, C12.2, C13.2, C14.2, C15.2, C16.2, C17.2, C18.2, C19.2, C20.2, C21.2, C22.2, C23.2, C24.1, C24.2, C25.2, C26.2, C27.2, C28.2, C29.2, R2.2, R9.2, R16.2, R20.2, R24.2, R26.2, R27.2, U1.16, U1.30, U1.31, U1.38, U1.51, U1.61, U1.71, U1.83, U1.94, U1.107, U1.120, U1.130, U1.143, U2.1, U2.6, U2.7, U3.4, U3.6, U3.8, U3.10, U3.12, U3.14, U3.16, U3.18, U3.20, U4.4, U4.7, U5.5, U5.6, U5.7, U5.8, U5.9, U6.1, U7.2, U8.2, U9.2, U10.6, U10.9, U11.2, U12.2, U14.C, U15.2, U15.3, U16.1, U16.3, U17.1
INPUT_USBPOWER_5V: C26.1, R28.2, U5.1, U6.4, U10.1, U10.2
NET_U1_6: C13.1, U1.6
NET_U1_25: R4.1, U1.25, U16.4
NET_U1_33: U1.32, U1.33
NET_U1_69: R7.1, U1.69, U4.6
NET_U1_70: R8.1, U1.70, U4.5
NET_U1_136: R5.1, U1.136, U2.13
NET_U1_137: R6.1, U1.137, U2.14
NET_U1_138: R9.1, U1.138
NET_U1_142: U13.3, U13.4
NET_U2_12: R10.1, U2.12
NET_U3_19: R16.1, U3.19
NET_U4_1: R17.1, U4.1
NET_U4_2: R18.1, U4.2
NET_U4_3: R19.1, U4.3
NET_U9_3: I1.1, U9.3
NET_U9_5: R20.1, R21.1, U9.5
NET_U9_ATNET_3: I1.2, R21.2
NET_U10_5: R28.1, U10.5
NET_U10_8: R27.1, U10.8
NET_U12_1: R23.1, R24.1, U12.1
NET_U12_3: R25.2, R26.1, U12.3
NET_U12_4: R22.1, U12.4, U15.4, U16.2
NET_U13_1: R2.1, U13.1, U13.2
PROC_ADC_IN2B: U1.50, U17.2
PROC_ADC_IN20: U1.75, U17.3
PROC_GPIO_TO_U2_INT1: U1.1, U2.4
PROC_SYS_JTCK_SWCLK: R14.1, U1.109, U3.9
PROC_SYS_JTDI: R12.1, U1.110, U3.5
PROC_SYS_JTDO_TRACESWO: U1.133, U3.13
PROC_SYS_JTMS_SWDIO: R13.1, U1.105, U3.7
PROC_SYS_JTRST: R11.1, U1.134, U3.3
PROC_USB_DM: U1.103, U5.2, U6.3
PROC_USB_DP: U1.104, U5.3, U6.2
RST_OUT_U3_SRESET_B: R15.1, U3.15, U15.1
VCC_S1_3V7: C23.1, C27.1, U9.4, U10.3, U10.4, U11.1
VCC_TIER1_3V3: C1.1, C2.1, C3.1, C4.1, C5.1, C6.1, C7.1, C8.1, C9.1, C10.1, C11.1, C12.1, C14.1, C15.1, C16.1, C17.1, C18.1, C19.1, C20.1, C21.1, C22.1, C24.2, C25.1, C28.1, C29.1, I1.2, R4.2, R5.2, R6.2, R7.2, R8.2, R10.2, R11.2, R12.2, R13.2, R14.2, R15.2, R17.2, R18.2, R19.2, R21.2, R22.2, R23.2, R25.1, U1.17, U1.33, U1.39, U1.52, U1.62, U1.72, U1.84, U1.95, U1.108, U1.121, U1.131, U1.144, U2.5, U2.8, U3.1, U3.2, U4.8, U7.4, U8.4, U12.6, U15.5, U16.5
